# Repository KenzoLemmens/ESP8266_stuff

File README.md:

# ESP8266_stuff
## Peripherals
* Olimex MOD-LCD2.8RTPD -> 2.8 LCD with touch and SPI interface

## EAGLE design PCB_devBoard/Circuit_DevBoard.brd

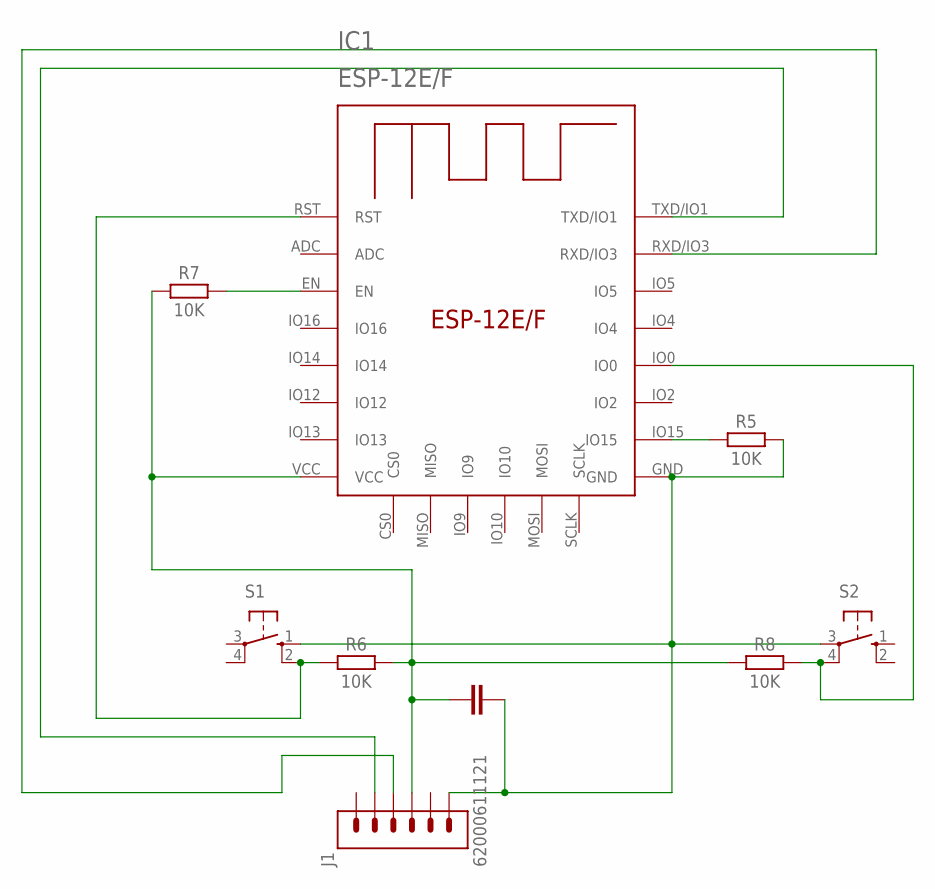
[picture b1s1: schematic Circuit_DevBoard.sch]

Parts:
IC1: ESP-12E/F; ESP-12E
J1: 62000611121
R5, R6, R7, R8: 10K; RESAD724W46L381D178B
S1, S2: 10-XX; B3F-10XX

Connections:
unnamed: IC1.EN, R7.2
unnamed: IC1.IO15, R5.1
unnamed: IC1.RST, R6.1, S1.2 (S1)
unnamed: IC1.GND, J1.6, R5.2, S1.1 (S), S2.3
unnamed: IC1.VCC, J1.4, R6.2, R7.1, R8.1
unnamed: IC1.IO0, R8.2, S2.4 (P1)
unnamed: IC1.RXD/IO3, J1.3
unnamed: IC1.TXD/IO1, J1.2

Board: 2 copper layers, 8 parts (0 on the bottom side), 8 nets, no tracks yet.

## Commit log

2021-05-23 Created "Arduino" folder
2021-05-23 Added datasheet
2021-05-24 Created initial version PCB design
2021-06-03 Create temp
